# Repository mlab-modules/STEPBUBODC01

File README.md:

# STEPBUBODC01A
Buck-boost convertor [TPS631000](https://www.ti.com/lit/ds/symlink/tps631000.pdf)

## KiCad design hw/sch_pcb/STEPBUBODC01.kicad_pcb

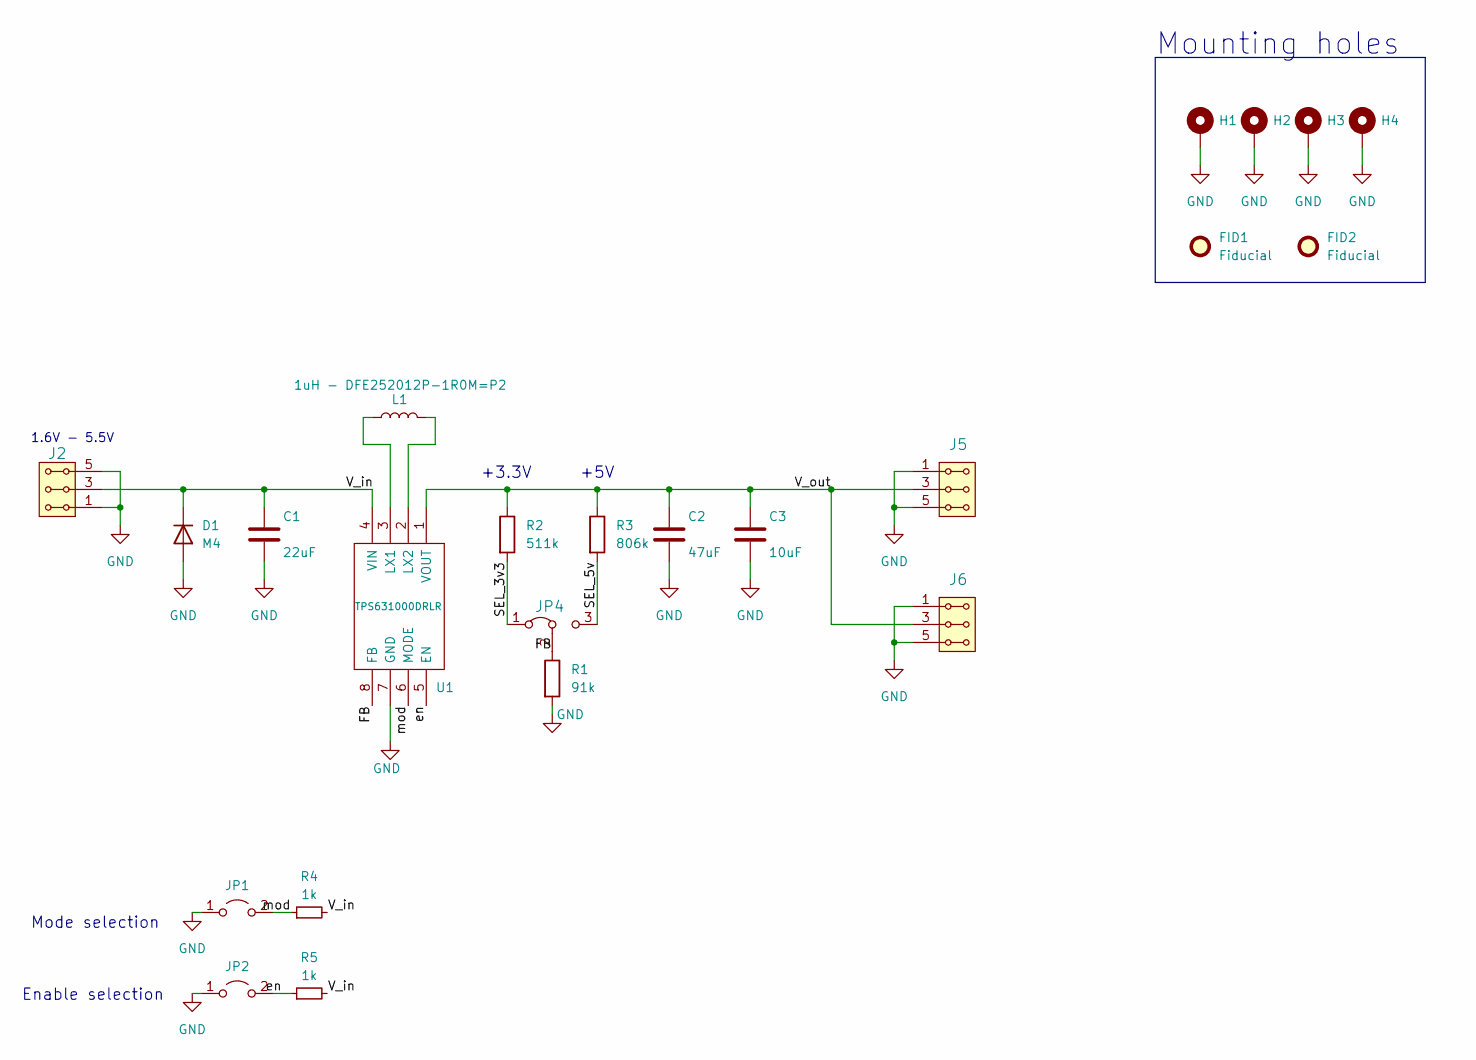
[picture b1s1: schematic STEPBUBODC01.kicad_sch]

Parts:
C1: 22uF; C_0805_2012Metric
C2: 47uF; C_0805_2012Metric
C3: 10uF; C_0805_2012Metric
D1: M4; D_SMA
FID1, FID2: Fiducial; Fiducial_1mm_Mask2mm
H1, H2, H3, H4: MountingHole_Pad; MountingHole_3mm
J2, J5, J6: HEADER_2x03_PARALLEL; PinHeader_2x03_P2.54mm_Vertical
JP1, JP2: Jumper_2_Open; PinHeader_1x02_P2.54mm_Vertical
JP4: HEADER_1x03; PinHeader_1x03_P2.54mm_Vertical
L1: 1uH - DFE252012P-1R0M=P2; L_1008_2520Metric
R1: 91k; R_0805_2012Metric
R2: 511k; R_0805_2012Metric
R3: 806k; R_0805_2012Metric
R4, R5: 1k; R_0805_2012Metric
U1: TPS631000DRLR; TPS631000; Mouser Part Number 595-TPS631000DRLR

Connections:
/FB: JP4.2 (C), R1.1, U1.8 (FB)
/SEL_3v3: JP4.1 (A), R2.2
/SEL_5v: JP4.3 (B), R3.2
/V_in: C1.1, D1.1 (K), J2.3, J2.4, R4.2, R5.2, U1.4 (VIN)
/V_out: C2.1, C3.1, J5.3, J5.4, J6.3, J6.4, R2.1, R3.1, U1.1 (VOUT)
/en: JP2.2 (B), R5.1, U1.5 (EN)
/mod: JP1.2 (B), R4.1, U1.6 (MODE)
GND: C1.2, C2.2, C3.2, D1.2 (A), H1.1, H2.1, H3.1, H4.1, J2.1, J2.2, J2.5, J2.6, J5.1, J5.2, J5.5, J5.6, J6.1, J6.2, J6.5, J6.6, JP1.1 (A), JP2.1 (A), R1.2, U1.7 (GND)
unnamed: L1.1, U1.3 (LX1)
unnamed: L1.2, U1.2 (LX2)

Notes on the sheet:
Mounting holes
Enable selection
+5V
Mode selection
1.6V - 5.5V
+3.3V

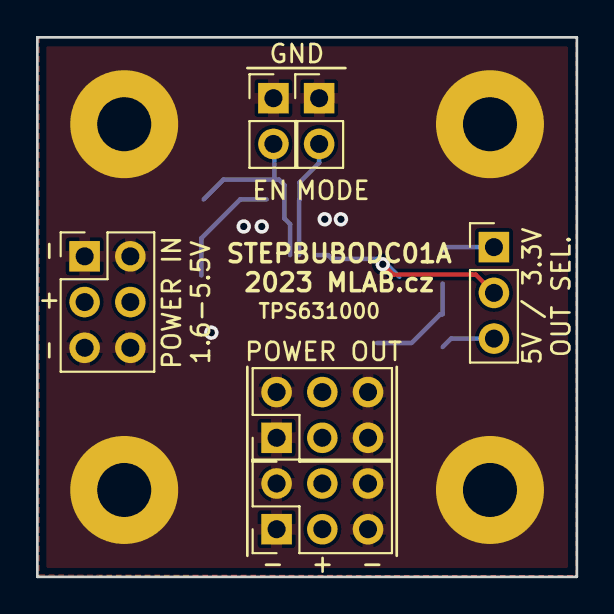
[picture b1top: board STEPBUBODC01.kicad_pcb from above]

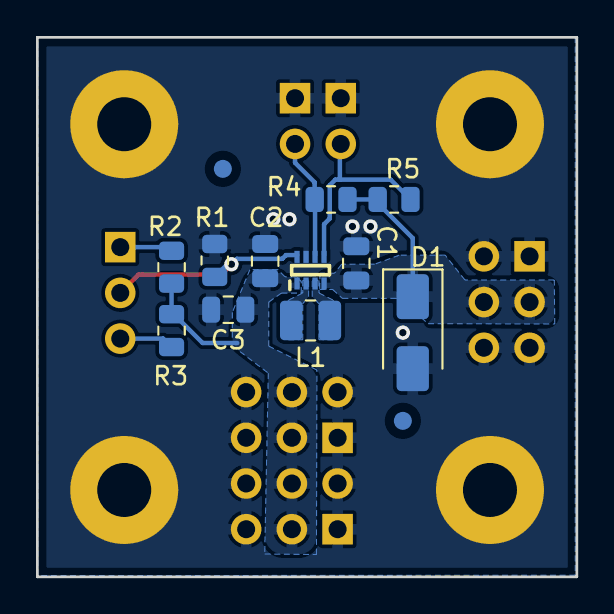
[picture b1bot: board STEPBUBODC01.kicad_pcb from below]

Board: 2 copper layers, 30.0 x 30.0 mm, 23 parts (13 on the bottom side), 10 nets.

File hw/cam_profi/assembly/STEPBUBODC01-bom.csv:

Component,Description,Part,References,Value,Footprint,Quantity Per PCB,Datasheet,ust_id,manufacturer_name,manufacturer_part_number,mouser part number,mouser price/stock
1,Unpolarized capacitor,C,C3,10uF,C_0805_2012Metric,1,~,5c70984712875079b91f8b53,,,,
2,Unpolarized capacitor,C,C1,22uF,C_0805_2012Metric,1,~,650b58f1462c6d9e7205463b,,,,
3,Unpolarized capacitor,C,C2,47uF,C_0805_2012Metric,1,~,5c70984812875079b91f8bbf,,,,
4,Diode,D,D1,M4,D_SMA,1,~,5c70984512875079b91f88ac,,,,
5,"2x03 2.54 mm pitch header, 2 pins next to each other are connected",HEADER_2x03_PARALLEL,J2J5J6,HEADER_2x03_PARALLEL,PinHeader_2x03_P2.54mm_Vertical,3,,,,,,
6,"Jumper, 3-pole, pins 1+2 closed/bridged",Jumper_3_Bridged12,JP4,HEADER_1x03,PinHeader_1x03_P2.54mm_Vertical,1,~,,,,,
7,"Jumper, 2-pole, open",Jumper_2_Open,JP1JP2,Jumper_2_Open,PinHeader_1x02_P2.54mm_Vertical,2,~,,,,,
8,Inductor,L,L1,1uH - DFE252012P-1R0M=P2,L_1008_2520Metric,1,~,650b5977462c6d9e72054656,,,,
9,"Resistor, small symbol",R_Small,R4R5,1k,R_0805_2012Metric,2,~,5c70984512875079b91f898c,,,,
10,Resistor,R,R1,91k,R_0805_2012Metric,1,~,650b59ec462c6d9e72054677,,,,
11,Resistor,R,R2,511k,R_0805_2012Metric,1,~,650b5a43462c6d9e7205468e,,,,
12,Resistor,R,R3,806k,R_0805_2012Metric,1,~,650b5abb462c6d9e720546b8,,,,
13,"Switching Voltage Regulators 1.5-A output current, high power density buck-boost converter",TPS631000DRLR,U1,TPS631000DRLR,SOTFL50P160X60-8N,1,https://www.ti.com/lit/ds/symlink/tps631000.pdf?ts=1652152702265,63de5ae4ae0b2d5aa05e2714,Texas Instruments,TPS631000DRLR,595-TPS631000DRLR,https://www.mouser.co.uk/ProductDetail/Texas-Instruments/TPS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

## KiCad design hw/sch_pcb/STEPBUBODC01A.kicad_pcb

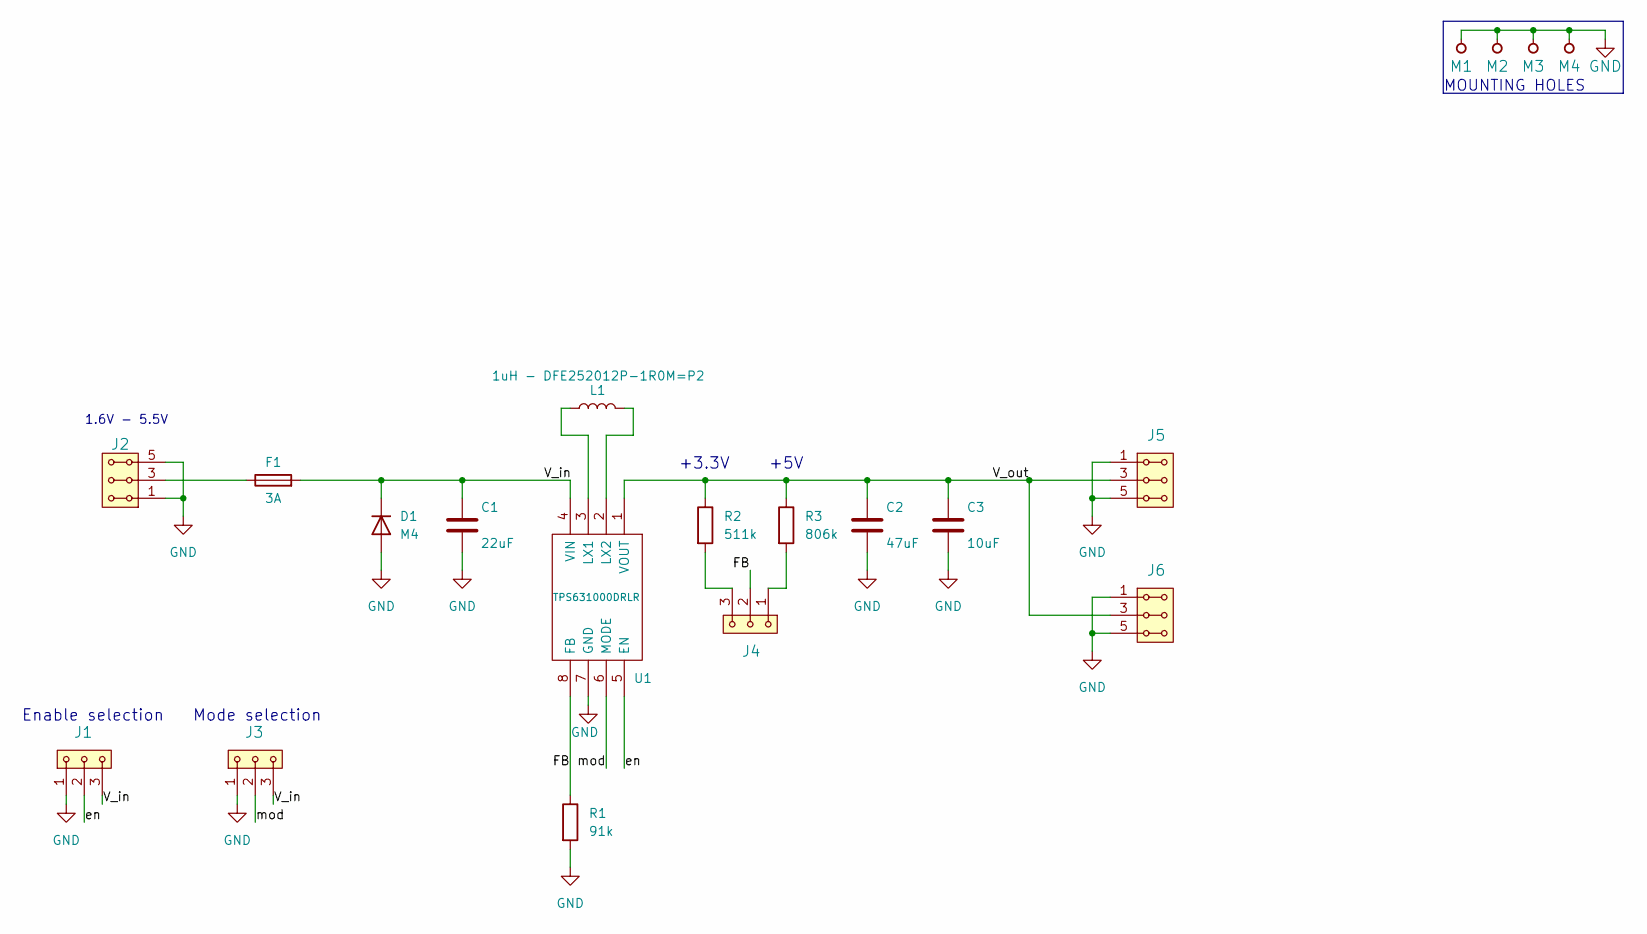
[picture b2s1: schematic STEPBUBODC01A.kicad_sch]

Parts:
C1: 22uF; SMD-0805
C2: 47uF; SMD-0805
C3: 10uF; SMD-0805
D1: M4
F1: 3A
J1, J3, J4: HEADER_1x03; Straight_1x03
J2, J5, J6: HEADER_2x03_PARALLEL; Straight_2x03
L1: 1uH - DFE252012P-1R0M=P2; L_1008_2520Metric
M1, M2: HOLE M3; MountingHole_3mm
M3, M4: HOLE; MountingHole_3mm
R1: 91k; SMD-0805
R2: 511k; SMD-0805
R3: 806k; SMD-0805
U1: TPS631000DRLR; SOTFL50P160X60-8N; Mouser Part Number 595-TPS631000DRLR

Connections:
/FB: J4.2, R1.1, U1.8 (FB)
/V_in: C1.1, D1.1 (K), F1.2, J1.3, J3.3, U1.4 (VIN)
/V_out: C2.1, C3.1, J5.3, J5.4, J6.3, J6.4, R2.1, R3.1, U1.1 (VOUT)
/en: J1.2, U1.5 (EN)
/mod: J3.2, U1.6 (MODE)
GND: C1.2, C2.2, C3.2, D1.2 (A), J1.1, J2.1, J2.2, J2.5, J2.6, J3.1, J5.1, J5.2, J5.5, J5.6, J6.1, J6.2, J6.5, J6.6, M1.1, M2.1, M3.1, M4.1, R1.2, U1.7 (GND)
unnamed: F1.1, J2.3, J2.4
unnamed: J4.1, R3.2
unnamed: J4.3, R2.2
unnamed: L1.1, U1.3 (LX1)
unnamed: L1.2, U1.2 (LX2)

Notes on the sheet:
MOUNTING HOLES
Enable selection
+5V
Mode selection
1.6V - 5.5V
+3.3V

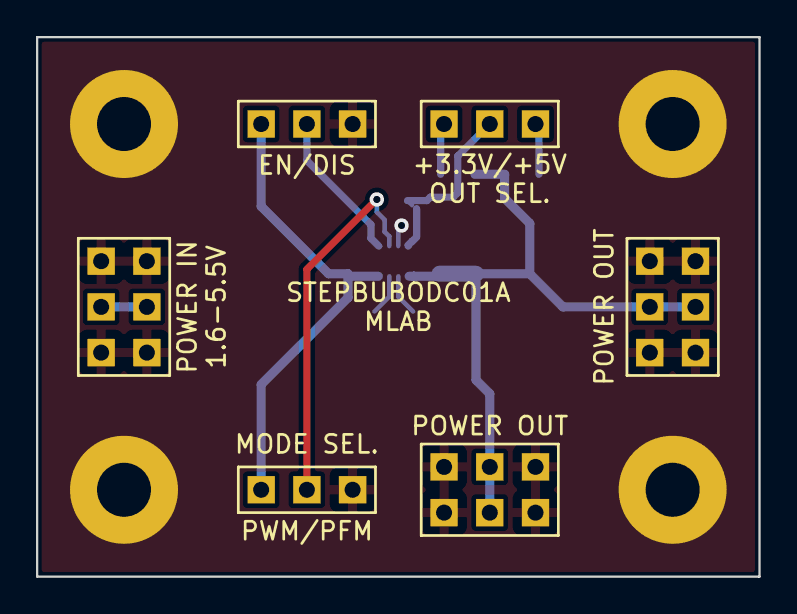
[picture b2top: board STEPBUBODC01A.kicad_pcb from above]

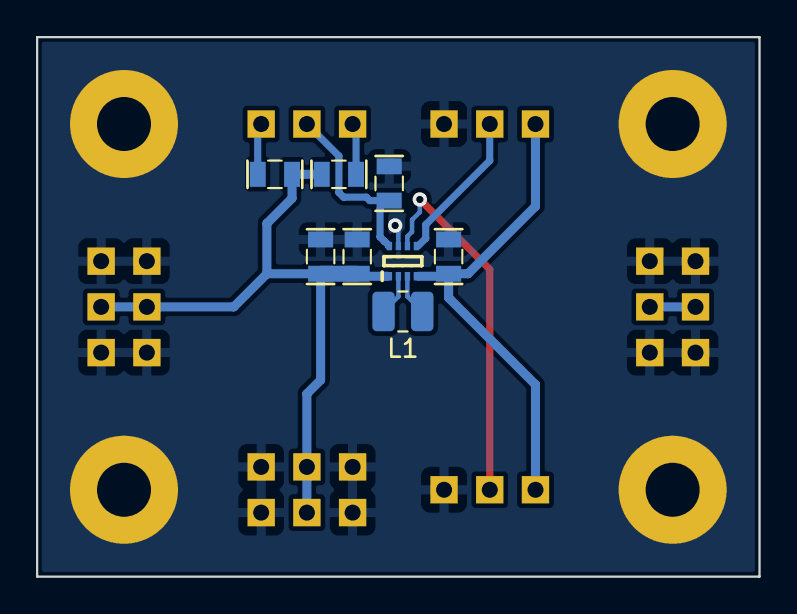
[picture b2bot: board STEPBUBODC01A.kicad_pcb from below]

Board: 2 copper layers, 40.1 x 30.0 mm, 18 parts (8 on the bottom side), 11 nets.

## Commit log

2023-01-12 Add files via upload
    KiCAD schematics
2023-01-16 footprints assigned
2023-01-16 pcb layout - 2 footprints missing
2023-01-17 PWM/PFM label added
2023-01-17 thicker traces
2023-01-18 Enable github actions. Update repository structure.
2023-01-18 Update actions products
2023-01-19 Update readme.
2023-01-20 silkscreen issues fixed
2023-04-13 pcb layout updated, ready for check
2023-04-13 mlab holes
2023-04-13 quatation added
2023-05-25 automated commit; add github actions
2023-05-25 Update metadata files
2023-05-28 Update workflow files
2023-07-05 automated commit; rename source files to new naming convence
2023-08-23 Improvements in schematics and layout, solve: #1, #2, #4
2023-09-16 Update image to image_title
2023-09-16 Update status
2023-09-17 Update metadata.yaml
    fix title image.
2023-09-20 add fidu, check layout, drc, update ust_id
2023-09-20 change USTID field
2023-09-20 update assets
2023-09-20 update workflows
2023-09-24 Kontrola a opravy pred vyrobou
2023-10-04 Edit B.Fab
